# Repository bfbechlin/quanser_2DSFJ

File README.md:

# quanser_2DSFJ

Projeto final para a disciplina de Microcontroladores.

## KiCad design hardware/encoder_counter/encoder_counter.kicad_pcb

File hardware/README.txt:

Esquemático para o projeto final.

Foi decidido modularizar o projeto em três PCIs:

- Driver Motor(NMOS Full bridge): controle do motor por onda PWM.
- Encoder Counters: leitura e contagem de ticks do encoder a leitura
	pela galileo é realizado pelo protocolo SPI.
- Galileo pins: shield para conexão com a placa.

Modularizando podemos dividir melhor as tarefas além de facilitar
os testes e debug do sistema como também diminui a complexidade do
roteamento no layout do circuito.

Os sensores de efeito Hall não foi encontrado exatamente em quais
pinos do cabo ICSI estão conectados e por isso foram colocados 
provisoriamente em dois pinos quaisquer.

Integrantes: Béuren Bechlin, Gabriel Ammes

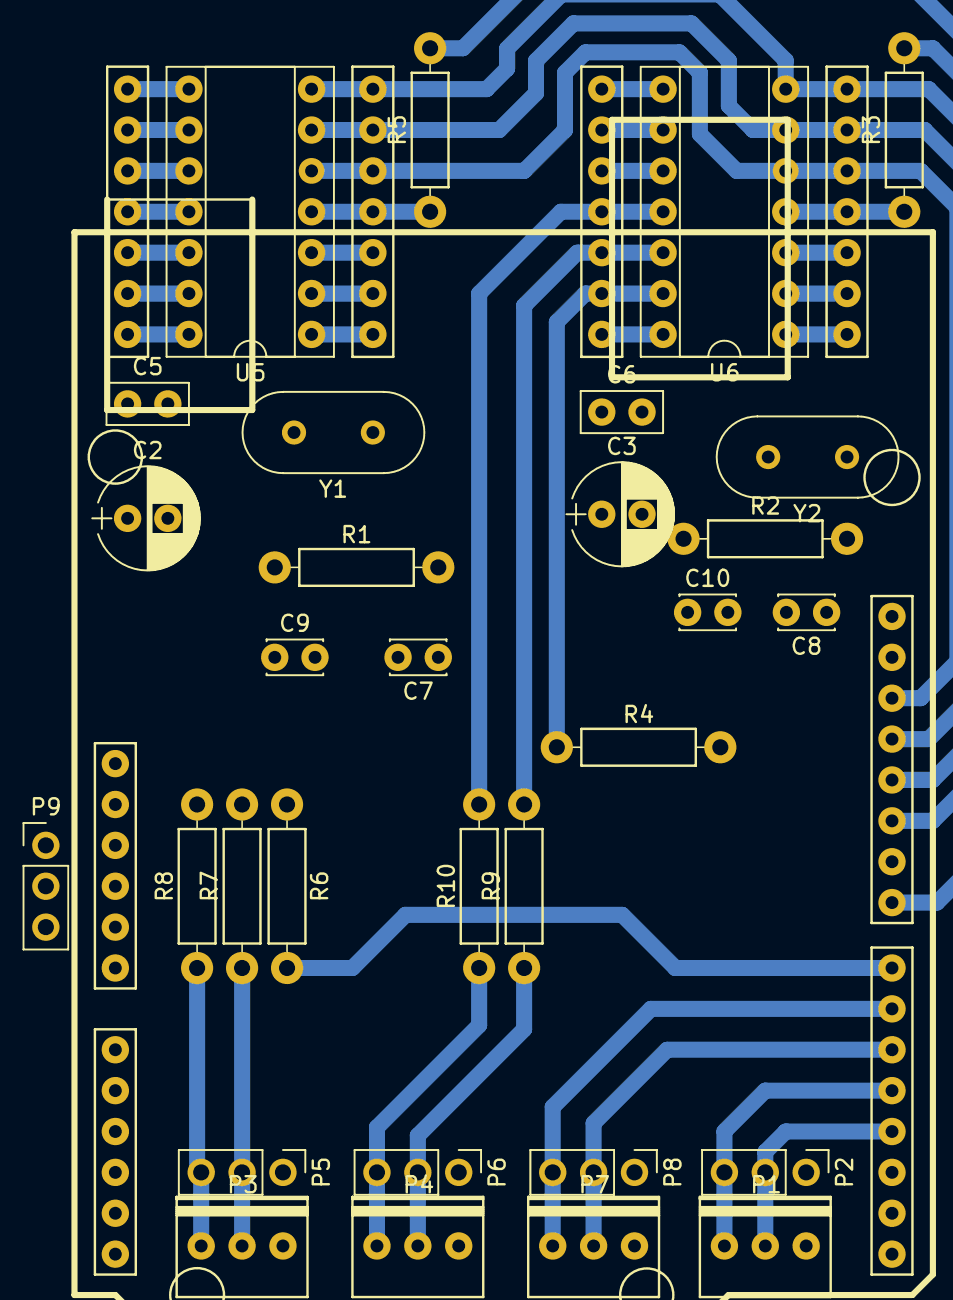
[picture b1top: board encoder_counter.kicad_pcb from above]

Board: 2 copper layers, 32 parts (0 on the bottom side), 29 nets.

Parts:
C2, C3: 10uF; CP_Radial_D6.3mm_P2.50mm
C5, C6: 0.1uF; C_Disc_D5.0mm_W2.5mm_P2.50mm
C7, C8, C9, C10: 22pF; C_Disc_D3.4mm_W2.1mm_P2.50mm
P1, P3, P4, P7: 5045-3; Molex_3Pin_180_TH
P2, P5, P6, P8, P9: FEMALE_HEADER; Pin_Header_Straight_1x03_Pitch2.54mm
R1, R2: 1M; Resistor_Horizontal_RM10mm_L7mm
R3, R4, R5, R6, R7, R8, R9, R10: 0; Resistor_Horizontal_RM10mm_L7mm
SHIELD1: ARDUINO_SHIELD
U5, U6: LS7366R; DIP-14_W15.24mm_Socket_Header
Y1, Y2: 32 MHz; Crystal_HC18-U_Vertical

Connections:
+5V: C2.1, C3.1, C5.1, C6.1, P9.1, SHIELD1.19, U5.14, U6.14
A_C1: P3.2, P5.2, R7.1
A_C2: P4.2, P6.2, R9.1
B_C1: P3.1, P5.3, R8.1
B_C2: P4.1, P6.3, R10.1
DRV_EN: P1.1, P2.3, SHIELD1.5
DRV_PWM: P1.2, P2.2, SHIELD1.4
EN_C1: R6.1, U5.13
EN_C2: R4.1, U6.13
GND: C2.2, C3.2, C5.2, C6.2, C7.2, C8.2, C9.2, C10.2, P1.3, P2.1, P3.3, P4.3, P5.1, P6.1, P7.3, P8.1, P9.2, P9.3, SHIELD1.15, SHIELD1.20, SHIELD1.21, U5.3, U6.3
LIMSW_1: P7.2, P8.2, SHIELD1.6
LIMSW_2: P7.1, P8.3, SHIELD1.7
MISO: SHIELD1.13, U5.6, U6.6
MOSI: SHIELD1.12, U5.7, U6.7
unnamed: C7.1, R1.2, U5.1, Y1.1
unnamed: C8.1, R2.2, U6.1, Y2.1
unnamed: C9.1, R1.1, U5.2, Y1.2
unnamed: C10.1, R2.1, U6.2, Y2.2
unnamed: R3.2, SHIELD1.11
unnamed: R4.2, SHIELD1.10
unnamed: R5.2, SHIELD1.9
unnamed: R6.2, SHIELD1.8
unnamed: R7.2, U5.12
unnamed: R8.2, U5.11
unnamed: R9.2, U6.12
unnamed: R10.2, U6.11
SCK: SHIELD1.14, U5.5, U6.5
SS_C1: R5.1, U5.4
SS_C2: R3.1, U6.4

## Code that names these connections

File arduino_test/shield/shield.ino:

#include <SPI.h>


/*
	Conection: http://bildr.org/2012/08/rotary-encoder-arduino/
*/

/***MDR0 configuration data - the configuration byte is formed with***
***single segments taken from each group and ORing all together.***/

//Count modes
#define NQUAD 			0x00	//non-quadrature mode
#define QUADRX1 		0x01	//X1 quadrature mode
#define QUADRX2 		0x02	//X2 quadrature mode
#define QUADRX4			0x03	//X4 quadrature mode
#define COUNT_MODE		0x03	//bits location in register
#define COUNT_SHIFT		0		//bit shift in register

//Running modes
#define FREE_RUN 		0x00
#define SINGE_CYCLE 	0x04
#define RANGE_LIMIT 	0x08
#define MODULO_N 		0x0C
#define RUNNING_MODE	0x0C	//bits location in register
#define RUNNING_SHIFT	2		//bit shift in register

//Index modes
#define DISABLE_INDX	0x00	//index_disabled
#define INDX_LOADC		0x10	//index_load_CNTR
#define INDX_RESETC		0x20	//index_rest_CNTR
#define INDX_LOADO		0x30    //index_load_OL
#define ASYNCH_INDX		0x00	//asynchronous index
#define SYNCH_INDX		0x40	//synchronous index
#define INDEX_MODE		0x70	//bits location in register
#define INDEX_SHIFT		4		//bit shift in register

//Clock filter modes
#define FILTER_1		0x00	//filter clock frequncy division factor 1
#define FILTER_2		0x80	//filter clock frequncy division factor 2
#define FILTER_MODE		0x80	//bits location in register
#define FILTER_SHIFT	7		//bit shift in register

/* **MDR1 configuration data; any of these***
  ***data segments can be ORed together***/

//Flag modes
#define NO_FLAGS		0x00	//all flags disabled
#define IDX_FLAG		0x10	//IDX flag
#define CMP_FLAG		0x20	//CMP flag
#define BW_FLAG 		0x40	//BW flag
#define CY_FLAG			0x80	//CY flag
#define FLAG_MODE		0xF0	//bits location in register
#define FLAG_SHIFT		4		//bit shift in register

//1 to 4 bytes data-width
#define BYTE_4 			0x00	//four byte mode
#define BYTE_3			0x01	//three byte mode
#define BYTE_2			0x02	//two byte mode
#define BYTE_1			0x03	//one byte mode
#define DATA_WID_MODE	0x03	//bits location in register
#define DATA_WID_SHIFT	0		//bit shift in register

//Enable/disable counter
#define EN_CNTR 		0x00	//counting enabled
#define DIS_CNTR 		0x04	//counting disabled
#define COUNT_EN_MODE	0x04	//bits location in register
#define COUNT_EN_SHIFT	2		//bit shift in register

/* LS7366R op-code list */
#define CLR_MDR0		0x08
#define CLR_MDR1		0x10
#define CLR_CNTR		0x20
#define CLR_STR			0x30
#define READ_MDR0		0x48
#define READ_MDR1		0x50
#define READ_CNTR		0x60
#define READ_OTR		0x68
#define READ_STR		0x70
#define WRITE_MDR1 		0x90
#define WRITE_MDR0		0x88
#define WRITE_DTR		0x98
#define LOAD_CNTR		0xE0
#define LOAD_OTR		0xE4


/* 2DFSJ Pin Header */
#define DRV_PWM 	3
#define DRV_EN 		4
#define LIM_SW1 	5
#define LIM_SW2 	6
#define EN_C2 		7
#define SS_C2 		8
#define EN_C1 		9
#define SS_C1 		10
#define MOSI		11
#define MISO		12
#define SCK			13

void LS7366R_clear(int ss_pin, unsigned char op_code)
{
	digitalWrite(ss_pin, HIGH);
	digitalWrite(ss_pin, LOW);

	SPI.transfer(op_code);

	digitalWrite(ss_pin, HIGH);
}

void LS7366R_write(int ss_pin, unsigned char op_code, unsigned char data)
{
	digitalWrite(ss_pin, HIGH);
	digitalWrite(ss_pin, LOW);

	SPI.transfer(op_code);
	SPI.transfer(data);

	digitalWrite(ss_pin, HIGH);
}

int LS7366R_read(int ss_pin, unsigned char op_code, int bytes)
{
	volatile unsigned int result = 0;
	volatile unsigned char data = 0;

	digitalWrite(ss_pin, HIGH);
	digitalWrite(ss_pin, LOW);

	SPI.transfer(op_code);
	for(int i = 0; i < bytes; i++){
		result = result << 8;
		data = SPI.transfer(0xFF);
		result = result | data;
	}

	digitalWrite(ss_pin, HIGH);
	return result;
}

void print_modes(unsigned char mode1, unsigned char mode2)
{
	Serial.println("MDR0 Modes:");
	Serial.print("Count: ");Serial.println((mode1 & COUNT_MODE) >> COUNT_SHIFT);
 	Serial.print("Runnig: ");Serial.println((mode1 & RUNNING_MODE) >> RUNNING_SHIFT);
	Serial.print("Index: ");Serial.println((mode1 & INDEX_MODE) >> INDEX_SHIFT);
	Serial.print("Filter: ");Serial.println((mode1 & FILTER_MODE) >> FILTER_SHIFT);


	Serial.println("MDR1 Modes");
	Serial.print("Data width: ");Serial.println((mode2 & DATA_WID_MODE) >> DATA_WID_SHIFT);
	Serial.print("Counter enable: ");Serial.println((mode2 & COUNT_EN_MODE) >> COUNT_EN_SHIFT);
	Serial.print("Flags: ");Serial.println((mode2 & FLAG_MODE) >> FLAG_SHIFT);
}

void setup()
{
	unsigned char mode1, mode2;

	Serial.begin(9600);
	SPI.begin();

	pinMode(DRV_EN, OUTPUT);
	pinMode(DRV_PWM, OUTPUT);

	pinMode(LIM_SW1, INPUT);
	pinMode(LIM_SW2, INPUT);
	digitalWrite(LIM_SW1, HIGH);
	digitalWrite(LIM_SW2, HIGH);


	digitalWrite(EN_C1, OUTPUT);
	digitalWrite(EN_C2, OUTPUT);

	digitalWrite(EN_C1, HIGH);
	digitalWrite(EN_C2, HIGH);

	SPI.setDataMode(SPI_MODE0);
    SPI.setBitOrder(MSBFIRST);
    SPI.setClockDivider(SPI_CLOCK_DIV2);
	//SPI.beginTransaction(SPISettings(4000000, MSBFIRST, SPI_MODE0));

	pinMode(SS_C1, OUTPUT);
	pinMode(SS_C2, OUTPUT);

	digitalWrite(SS_C1, HIGH);
	digitalWrite(SS_C2, HIGH);

	LS7366R_clear(SS_C1, CLR_CNTR);
	LS7366R_clear(SS_C2, CLR_CNTR);

	mode1 = QUADRX4|FREE_RUN|DISABLE_INDX|FILTER_2;
	mode2 = BYTE_2|EN_CNTR|NO_FLAGS;

	LS7366R_write(SS_C1, WRITE_MDR0, mode1);
	LS7366R_write(SS_C1, WRITE_MDR1, mode2);

	LS7366R_write(SS_C2, WRITE_MDR0, mode1);
	LS7366R_write(SS_C2, WRITE_MDR1, mode2);

	Serial.println("Encoder 1 :");
	mode1 = LS7366R_read(SS_C1, READ_MDR0, 1);
	mode2 = LS7366R_read(SS_C2, READ_MDR1, 1);
	print_modes(mode1, mode2);

	Serial.println("Encoder 2 :");
	mode1 = LS7366R_read(SS_C1, READ_MDR0, 1);
	mode2 = LS7366R_read(SS_C2, READ_MDR1, 1);
	print_modes(mode1, mode2);

}

void loop(){

	Serial.print("Counter1 ::: ");
	Serial.print(LS7366R_read(SS_C1, READ_CNTR, 2)/4);
	Serial.print(" Limit Switch 1:::");
	Serial.println(digitalRead(LIM_SW1));

	Serial.print("Counter 2 ::: ");
	Serial.print(LS7366R_read(SS_C2, READ_CNTR, 2)/4);
	Serial.print(" Limit Switch 2:::");
	Serial.println(digitalRead(LIM_SW2));

	if(Serial.available() > 0){
		char buff = Serial.read();
		if(buff == ('r' | 'R')){
			LS7366R_clear(SS_C1, CLR_CNTR);
			LS7366R_clear(SS_C2, CLR_CNTR);
		}
	}

	analogWrite(DRV_PWM, (LS7366R_read(SS_C1, READ_CNTR, 2)/4) % 256);
	digitalWrite(DRV_EN, !digitalRead(LIM_SW1));
	delay(1000);
}

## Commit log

2017-05-31 Setting up repository and add hardware project files.
2017-07-16 Added PID, LS7366R lib and layout off DC Motor Driver PCB and Arduino Shied PCB.
2017-08-31 Last version.
2017-12-29 Final version after some research in working folders.
